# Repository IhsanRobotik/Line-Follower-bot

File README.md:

# PID Line Follower Bot

A two-wheel line follower built around an ATmega32A microcontroller, optical line sensors, and dual L298N motor drivers. The KiCad design includes the controller, sensor and motor-control circuits, and a compact robot PCB.

## Hardware overview

- ATmega32A-P microcontroller with crystal, buzzer, pushbuttons, and LCD connector
- Six photodetector inputs with LED emitters for line sensing
- Two L298N H-bridge drivers for the left and right DC motors
- 12 V input with an LM7809 regulator for the logic supply

## PCB and schematic

## KiCad source files

- [KiCad project](PID%20Line%20Follower.kicad_pro)
- [Schematic](PID%20Line%20Follower.kicad_sch)
- [PCB layout](PID%20Line%20Follower.kicad_pcb)

## Exports

- [PCB STEP model](exports/3d/PID%20Line%20Follower.step)
- [IDF board file](exports/idf/PID%20Line%20Follower.emn)
- [IDF library file](exports/idf/PID%20Line%20Follower.emp)

PDF drawing exports: [BOT](exports/pdf/BOT.pdf), [BOT NO MIRROR](exports/pdf/BOT%20NO%20MIRROR.pdf), [BOT 3](exports/pdf/BOT%203.pdf), [bot 4](exports/pdf/bot%204.pdf), [bot 5](exports/pdf/bot%205.pdf), [bot 6](exports/pdf/bot%206.pdf), and [bot5](exports/pdf/bot5.pdf).

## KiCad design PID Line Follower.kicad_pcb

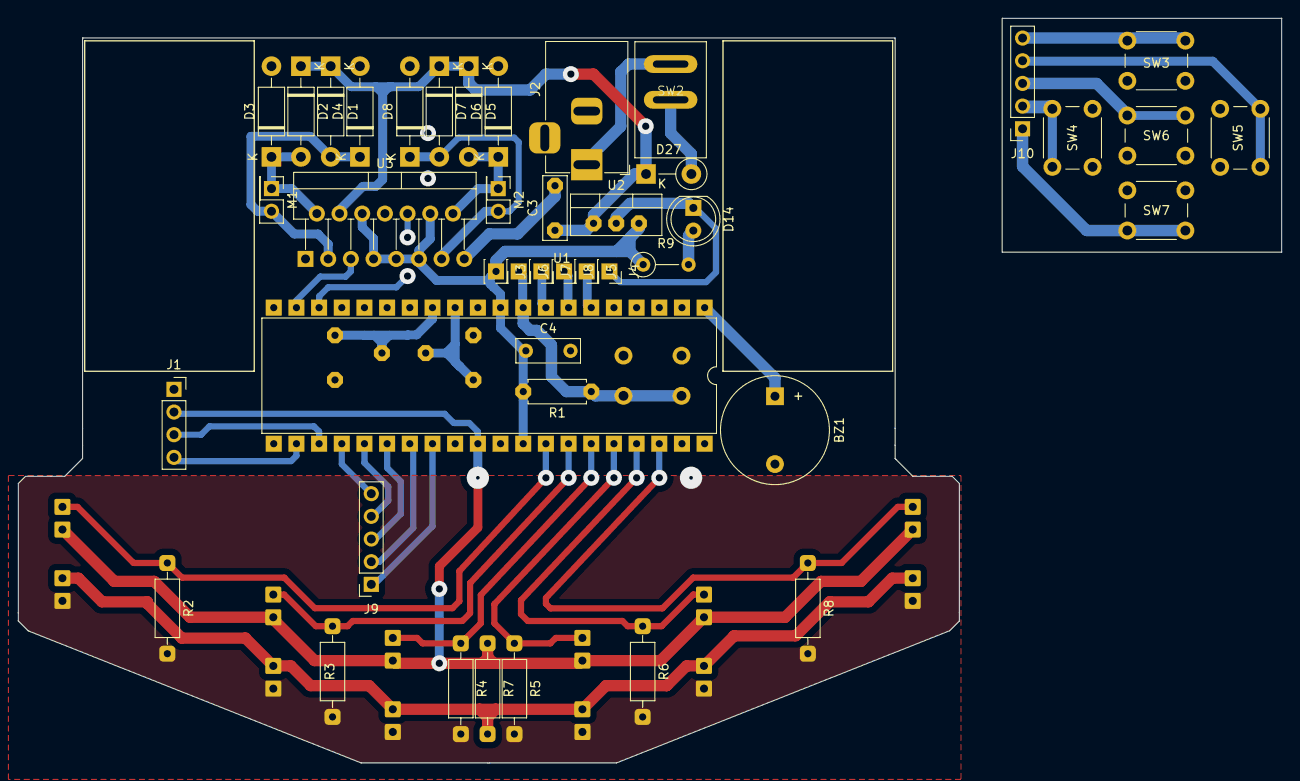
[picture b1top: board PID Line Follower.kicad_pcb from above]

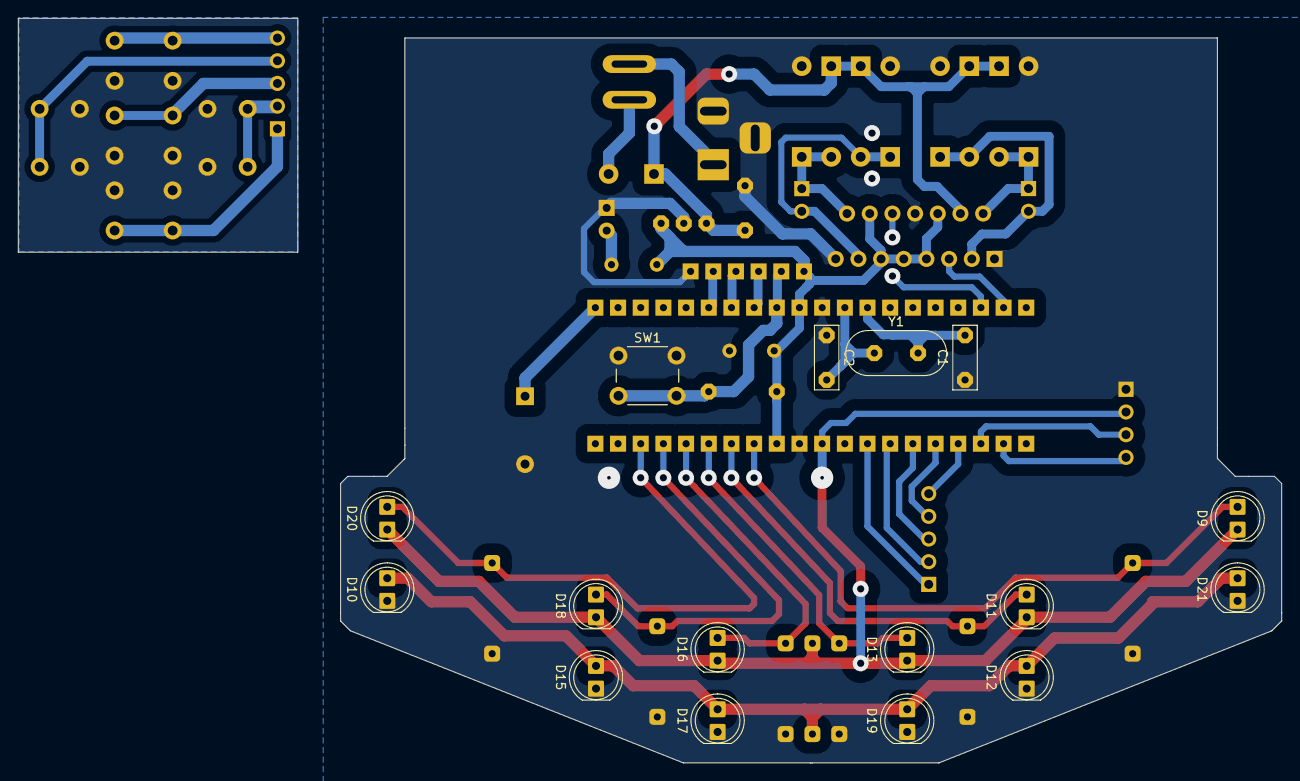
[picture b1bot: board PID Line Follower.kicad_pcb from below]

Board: 2 copper layers, 105.4 x 81.2 mm, 59 parts (16 on the bottom side), 38 nets.

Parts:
BZ1: Buzzer; Buzzer_12x9.5RM7.6
C1, C2: 0.33 uF; C_Disc_D7.0mm_W2.5mm_P5.00mm
C3: 0.33uF; C_Disc_D7.0mm_W2.5mm_P5.00mm
C4: 0.1uF; C_Disc_D7.0mm_W2.5mm_P5.00mm
D1, D2, D3, D4, D5, D6, D7, D8: 1N4007; D_DO-41_SOD81_P10.16mm_Horizontal
D9, D11, D13, D16, D18, D20: D_Photo; LED_D5.0mm
D10, D12, D14, D15, D17, D19, D21: LED; LED_D5.0mm
D27: 1N4001; D_DO-41_SOD81_P5.08mm_Vertical_KathodeUp
J1: LCD; PinSocket_1x04_P2.54mm_Vertical
J2: Barrel_Jack; BarrelJack_Horizontal
J3, J4, J5, J6, J7, J8: Conn_01x01_Pin; PinSocket_1x01_P2.54mm_Vertical
J9, J10: Conn_01x05_Pin; PinSocket_1x05_P2.54mm_Vertical
M1, M2: Motor_DC; PinHeader_2x01_P2.54mm_Vertical
R1: R; R_Axial_DIN0207_L6.3mm_D2.5mm_P7.62mm_Horizontal
R2, R3, R4, R5, R6, R8: R; R_Axial_DIN0207_L6.3mm_D2.5mm_P10.16mm_Horizontal
R7: 47R; R_Axial_DIN0207_L6.3mm_D2.5mm_P10.16mm_Horizontal
R9: 220; R_Axial_DIN0207_L6.3mm_D2.5mm_P5.08mm_Vertical
SW1, SW3, SW4, SW5, SW6, SW7: SW_SPST; SW_PUSH_6mm
SW2: SW_SPST; switch
U1: ATmega32A-P; DIP-40_W15.24mm
U2: LM7809; TO-220-3_Vertical
U3: L298N; TO-220-15_P2.54x2.54mm_StaggerOdd_Lead4.58mm_Vertical
Y1: Crystal; Crystal_HC18-U_Vertical

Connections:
2: D9.2 (A), R2.1, U1.33 (PA7)
3: D11.2 (A), R3.1, U1.34 (PA6)
4: D13.2 (A), R4.1, U1.35 (PA5)
5: D16.2 (A), R5.1, U1.36 (PA4)
6: D18.2 (A), R6.1, U1.37 (PA3)
7: D20.2 (A), R8.1, U1.38 (PA2)
+12V: C3.1, D1.1 (K), D2.1 (K), D5.1 (K), D7.1 (K), D27.1 (K), U2.1 (VI), U3.4 (Vs)
GND: BZ1.2 (-), C1.1, C2.1, C3.2, C4.2, D3.2 (A), D4.2 (A), D6.2 (A), D8.2 (A), D10.1 (K), D12.1 (K), D14.1 (K), D15.1 (K), D17.1 (K), D19.1 (K), D21.1 (K), J1.1, J2.2, J2.3, J4.1, R2.2, R3.2, R4.2, R5.2, R6.2, R8.2, SW1.1 (A), SW3.1 (A), SW4.1 (A), SW5.1 (A), SW6.1 (A), SW7.1 (A), U1.11 (GND), U1.31 (GND), U2.2 (GND), U3.1 (SENSE_A), U3.8 (GND), U3.15 (SENSE_B)
MISO: J8.1, U1.7 (PB6)
MOSI: J5.1, U1.6 (PB5)
MOTOR 1: U1.19 (PD5), U3.5 (IN1)
MOTOR 2: U1.18 (PD4), U3.10 (IN3)
unnamed: BZ1.1 (+), U1.1 (PB0)
unnamed: D1.2 (A), D4.1 (K), M1.2 (-), U3.3 (OUT2)
unnamed: D2.2 (A), D3.1 (K), M1.1 (+), U3.2 (OUT1)
unnamed: D5.2 (A), D6.1 (K), M2.1 (+), U3.14 (OUT4)
unnamed: D7.2 (A), D8.1 (K), M2.2 (-), U3.13 (OUT3)
unnamed: D10.2 (A), D12.2 (A), D15.2 (A), D17.2 (A), D19.2 (A), D21.2 (A), R7.2
unnamed: D14.2 (A), R9.2
unnamed: D27.2 (A), SW2.2 (B)
unnamed: J9.1, U1.28 (PC6)
unnamed: J9.2, U1.27 (PC5)
unnamed: J9.3, U1.26 (PC4)
unnamed: J9.4, U1.25 (PC3)
unnamed: J9.5, U1.24 (PC2)
unnamed: J10.1, SW7.2 (B)
unnamed: J10.2, SW4.2 (B)
unnamed: J10.3, SW6.2 (B)
unnamed: J10.4, SW5.2 (B)
unnamed: J10.5, SW3.2 (B)
unnamed: J2.1, SW2.1 (A)
unnamed: C1.2, U1.13 (XTAL1), Y1.2
unnamed: C2.2, U1.12 (XTAL2), Y1.1
RESET: J6.1, R1.1, SW1.2 (B), U1.9 (~RESET)
SCK: J7.1, U1.8 (PB7)
SCL: J1.4, U1.22 (PC0)
SDA: J1.3, U1.23 (PC1)
VCC: C4.1, D9.1 (K), D11.1 (K), D13.1 (K), D16.1 (K), D18.1 (K), D20.1 (K), J1.2, J3.1, R1.2, R7.1, R9.1, U1.10 (VCC), U1.30 (AVCC), U1.32 (AREF), U2.3 (VO), U3.6 (EnA), U3.7 (IN2), U3.9 (Vss), U3.11 (EnB), U3.12 (IN4)
